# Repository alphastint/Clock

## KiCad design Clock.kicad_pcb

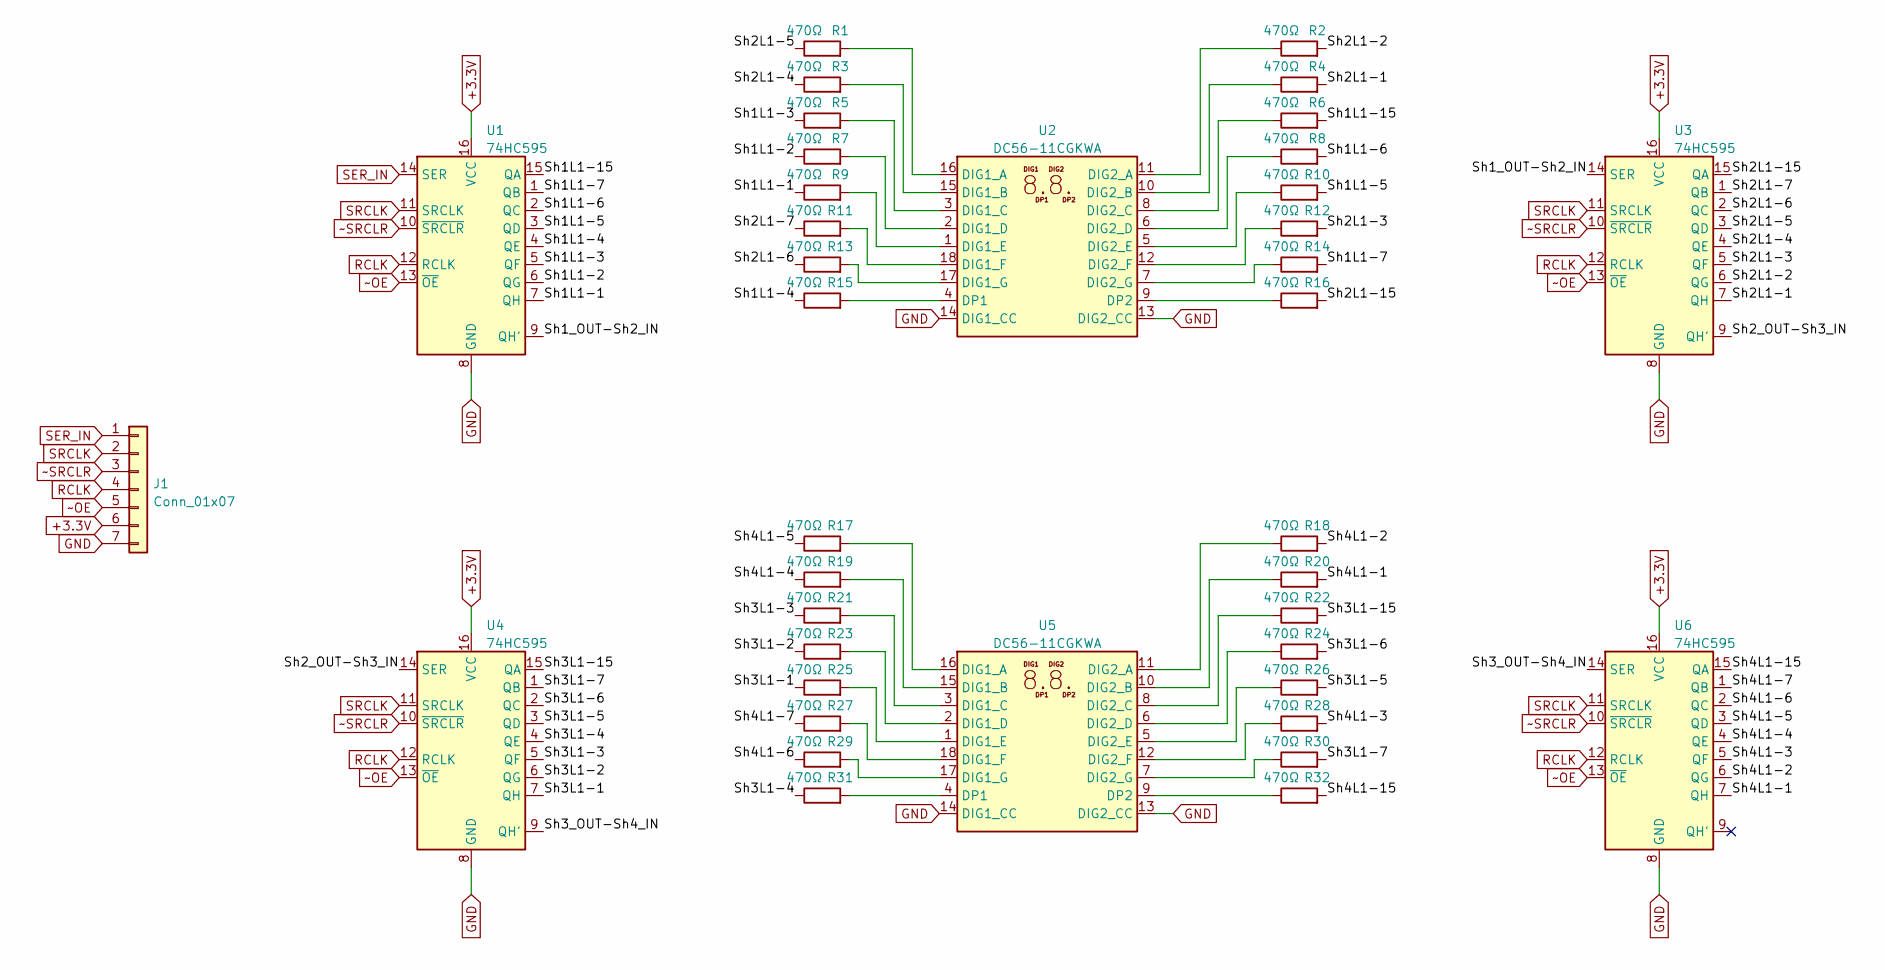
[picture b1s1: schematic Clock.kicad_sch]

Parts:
J1: Conn_01x07; PinHeader_1x07_P2.54mm_Vertical
R1, R2, R3, R4, R5, R6, R7, R8, R9, R10, R11, R12, R13, R14, R15, R16, R17, R18, R19, R20, R21, R22, R23, R24, R25, R26, R27, R28, R29, R30, R31, R32: 470Ω; R_0603_1608Metric_Pad0.98x0.95mm_HandSolder
U1, U3, U4, U6: 74HC595; SO-16_3.9x9.9mm_P1.27mm
U2, U5: DC56-11CGKWA; DA56-11CGKWA

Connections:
+3.3V: J1.6, U1.16 (VCC), U3.16 (VCC), U4.16 (VCC), U6.16 (VCC)
/Sh1L1-1: R9.1, U1.7 (QH)
/Sh1L1-2: R7.1, U1.6 (QG)
/Sh1L1-3: R5.1, U1.5 (QF)
/Sh1L1-4: R15.1, U1.4 (QE)
/Sh1L1-5: R10.2, U1.3 (QD)
/Sh1L1-6: R8.2, U1.2 (QC)
/Sh1L1-7: R14.2, U1.1 (QB)
/Sh1L1-15: R6.2, U1.15 (QA)
/Sh1_OUT-Sh2_IN: U1.9 (QH'), U3.14 (SER)
/Sh2L1-1: R4.2, U3.7 (QH)
/Sh2L1-2: R2.2, U3.6 (QG)
/Sh2L1-3: R12.2, U3.5 (QF)
/Sh2L1-4: R3.1, U3.4 (QE)
/Sh2L1-5: R1.1, U3.3 (QD)
/Sh2L1-6: R13.1, U3.2 (QC)
/Sh2L1-7: R11.1, U3.1 (QB)
/Sh2L1-15: R16.2, U3.15 (QA)
/Sh2_OUT-Sh3_IN: U3.9 (QH'), U4.14 (SER)
/Sh3L1-1: R25.1, U4.7 (QH)
/Sh3L1-2: R23.1, U4.6 (QG)
/Sh3L1-3: R21.1, U4.5 (QF)
/Sh3L1-4: R31.1, U4.4 (QE)
/Sh3L1-5: R26.2, U4.3 (QD)
/Sh3L1-6: R24.2, U4.2 (QC)
/Sh3L1-7: R30.2, U4.1 (QB)
/Sh3L1-15: R22.2, U4.15 (QA)
/Sh3_OUT-Sh4_IN: U4.9 (QH'), U6.14 (SER)
/Sh4L1-1: R20.2, U6.7 (QH)
/Sh4L1-2: R18.2, U6.6 (QG)
/Sh4L1-3: R28.2, U6.5 (QF)
/Sh4L1-4: R19.1, U6.4 (QE)
/Sh4L1-5: R17.1, U6.3 (QD)
/Sh4L1-6: R29.1, U6.2 (QC)
/Sh4L1-7: R27.1, U6.1 (QB)
/Sh4L1-15: R32.2, U6.15 (QA)
GND: J1.7, U1.8 (GND), U2.13 (DIG2_CC), U2.14 (DIG1_CC), U3.8 (GND), U4.8 (GND), U5.13 (DIG2_CC), U5.14 (DIG1_CC), U6.8 (GND)
unnamed: R1.2, U2.16 (DIG1_A)
unnamed: R2.1, U2.11 (DIG2_A)
unnamed: R3.2, U2.15 (DIG1_B)
unnamed: R4.1, U2.10 (DIG2_B)
unnamed: R5.2, U2.3 (DIG1_C)
unnamed: R6.1, U2.8 (DIG2_C)
unnamed: R7.2, U2.2 (DIG1_D)
unnamed: R8.1, U2.6 (DIG2_D)
unnamed: R9.2, U2.1 (DIG1_E)
unnamed: R10.1, U2.5 (DIG2_E)
unnamed: R11.2, U2.18 (DIG1_F)
unnamed: R12.1, U2.12 (DIG2_F)
unnamed: R13.2, U2.17 (DIG1_G)
unnamed: R14.1, U2.7 (DIG2_G)
unnamed: R15.2, U2.4 (DP1)
unnamed: R16.1, U2.9 (DP2)
unnamed: R17.2, U5.16 (DIG1_A)
unnamed: R18.1, U5.11 (DIG2_A)
unnamed: R19.2, U5.15 (DIG1_B)
unnamed: R20.1, U5.10 (DIG2_B)
unnamed: R21.2, U5.3 (DIG1_C)
unnamed: R22.1, U5.8 (DIG2_C)
unnamed: R23.2, U5.2 (DIG1_D)
unnamed: R24.1, U5.6 (DIG2_D)
unnamed: R25.2, U5.1 (DIG1_E)
unnamed: R26.1, U5.5 (DIG2_E)
unnamed: R27.2, U5.18 (DIG1_F)
unnamed: R28.1, U5.12 (DIG2_F)
unnamed: R29.2, U5.17 (DIG1_G)
unnamed: R30.1, U5.7 (DIG2_G)
unnamed: R31.2, U5.4 (DP1)
unnamed: R32.1, U5.9 (DP2)
RCLK: J1.4, U1.12 (RCLK), U3.12 (RCLK), U4.12 (RCLK), U6.12 (RCLK)
SER_IN: J1.1, U1.14 (SER)
SRCLK: J1.2, U1.11 (SRCLK), U3.11 (SRCLK), U4.11 (SRCLK), U6.11 (SRCLK)
~OE: J1.5, U1.13 (~OE), U3.13 (~OE), U4.13 (~OE), U6.13 (~OE)
~SRCLR: J1.3, U1.10 (~SRCLR), U3.10 (~SRCLR), U4.10 (~SRCLR), U6.10 (~SRCLR)

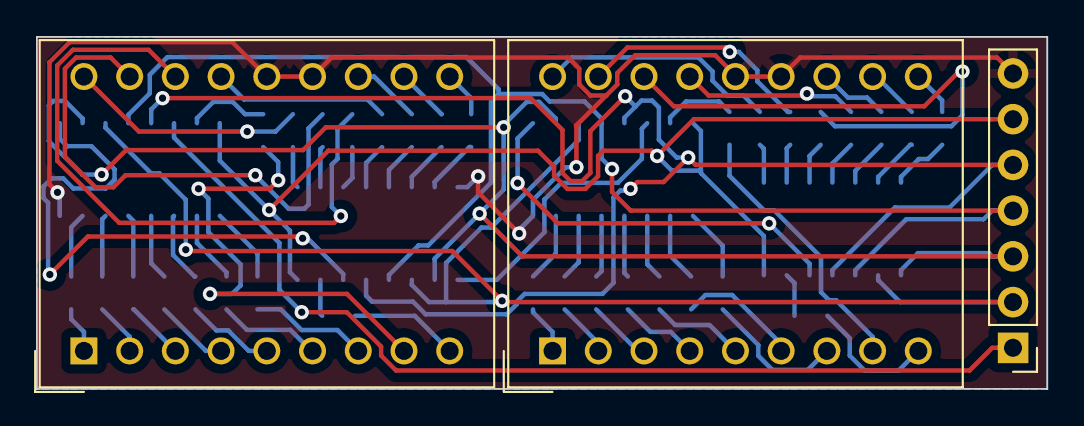
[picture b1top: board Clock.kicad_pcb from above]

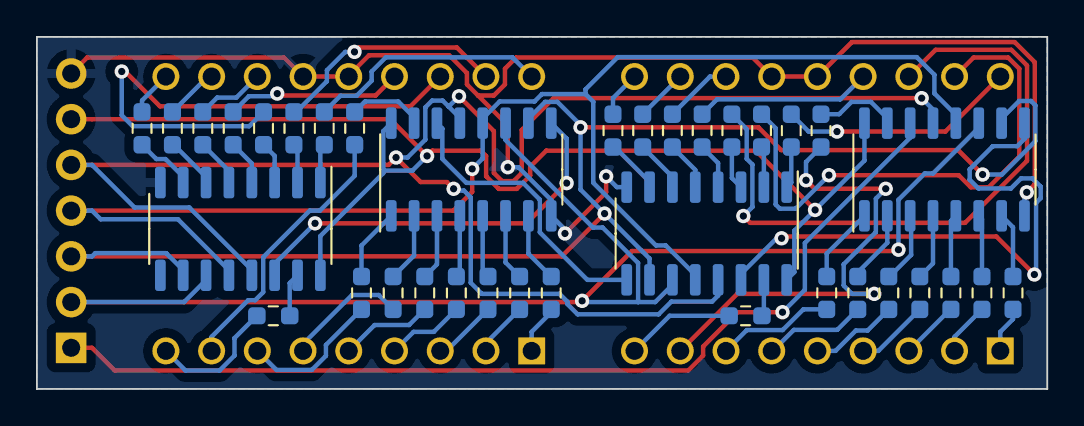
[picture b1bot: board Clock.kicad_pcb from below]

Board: 2 copper layers, 56.1 x 19.6 mm, 39 parts (36 on the bottom side), 74 nets.

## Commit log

2025-04-30 ver2.0 production
2025-05-12 schematic
